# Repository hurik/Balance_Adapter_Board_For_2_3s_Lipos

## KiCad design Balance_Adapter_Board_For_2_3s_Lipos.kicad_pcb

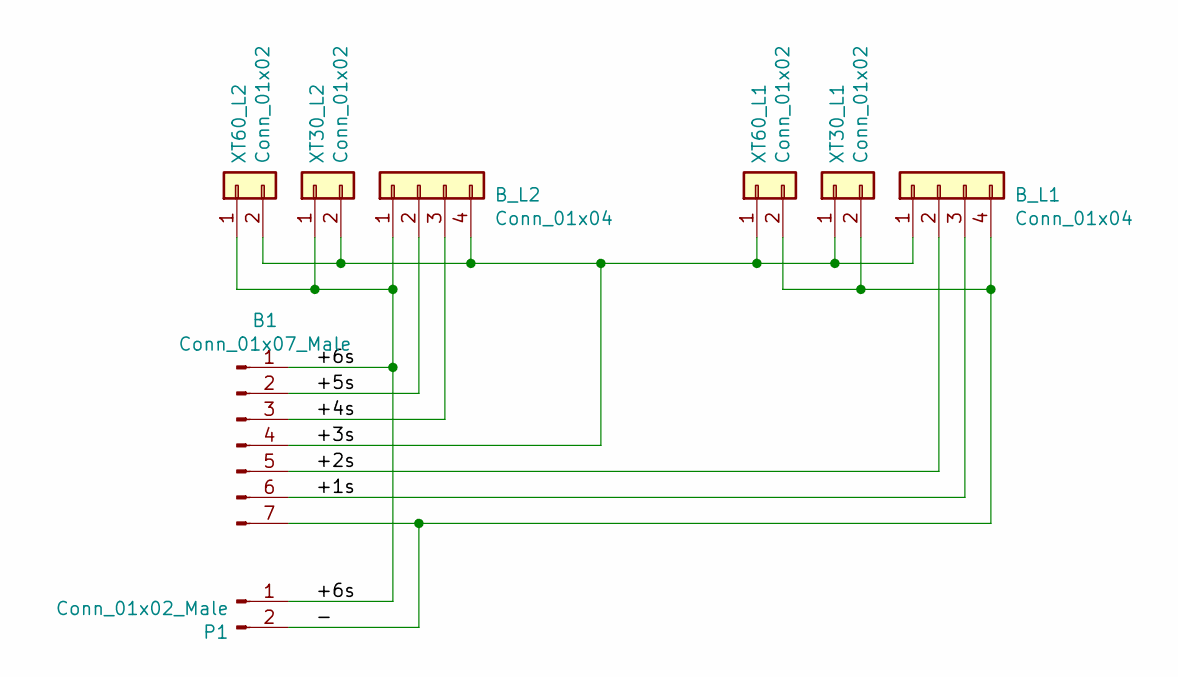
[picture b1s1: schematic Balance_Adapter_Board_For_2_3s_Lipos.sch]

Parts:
B1: Conn_01x07_Male; Pin_Header_Straight_1x07_Pitch2.54mm
B_L1, B_L2: Conn_01x04; JST_XH_B04B-XH-A_04x2.50mm_Straight
P1: Conn_01x02_Male; PowerCable
XT30_L1, XT30_L2: Conn_01x02; XT30
XT60_L1, XT60_L2: Conn_01x02; XT60

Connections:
/+1s: B1.6, B_L1.3
/+2s: B1.5, B_L1.2
/+3s: B1.4, B_L1.1, B_L2.4, XT30_L1.1, XT30_L2.2, XT60_L1.1, XT60_L2.2
/+4s: B1.3, B_L2.3
/+5s: B1.2, B_L2.2
/+6s: B1.1, B_L2.1, P1.1, XT30_L2.1, XT60_L2.1
/-: B1.7, B_L1.4, P1.2, XT30_L1.2, XT60_L1.2

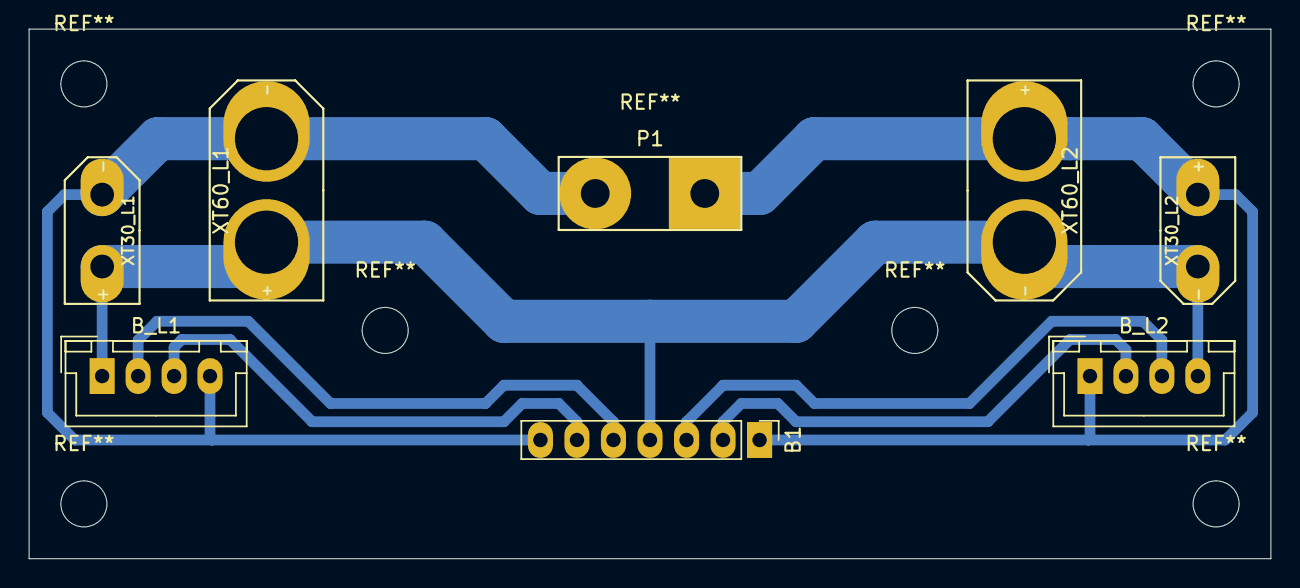
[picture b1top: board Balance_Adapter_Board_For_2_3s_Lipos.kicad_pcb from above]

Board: 2 copper layers, 86.4 x 36.8 mm, 8 parts (0 on the bottom side), 7 nets.

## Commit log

2019-05-06 improved
2019-05-06 improved layout for more safety
2019-05-06 changed spacing between xt60 and xt30
2019-05-06 added baseplate
2019-05-07 improved pads and balancer traces
2019-05-07 changed track width again and routing
2019-05-07 improved XT30 and XT60 footprints
2019-05-08 minor XT30 improvement
2019-09-19 better design
2019-09-23 now symmetrical and more space between XT30 and XT60
